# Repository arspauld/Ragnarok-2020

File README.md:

# Ragnarok-2020
Repository containing all software and electronics for the 2020 International CanSat Competition Team Ragnarok. Software is based around the STM32 family of ARM microcontrollers. All electronics are designed to meet the mission requirements described [here](http://cansatcompetition.com/docs/CanSat_Mission_Guide_2020.pdf).

__All mission reviews and documentation are currently hosted separately__.

### Software
#### Pat needs to fill this in
Development is being done in VSCode using the PlatformIO extension.
Requirements/configuration: _something about python, pip, pyserial, etc..._
`sudo apt-get install python3 -m pip`
`pip3 install pyserial`

Software team:
- Patrick Smith (lead)
- Noah Schwalb

For more information about software development contact __PATS INFO HERE__

### Electrical
Electrical development is completed using [KiCad](http://www.kicad.org).

#### Documentation
The directory `/hardware/documentation/` contains important datasheets and application notes for the microcontrollers and components to be used within this project. These documents contain application specific information, and they should contain answers to any questions that may be had about these components.

#### Trade studies
The directory `/hardware/trade-studies/` contains datasheets for each of the sensors considered in this project. Detailed trade-studies have been completed and are hosted outside of this repository.

#### Libraries
The directory `/hardware/libraries/` contains the part libraries to be used within each of the PCBs. These libraries will include schematic symbols and physical footprints for each component. Libraries are first drawn from the [KiCad](http://kicad.org/libraries/download/) standard library and [Digikey-KiCad](https://www.digikey.com/en/resources/design-tools/kicad) standard library. If a symbol or footprint is missing from this library, [SnapEDA](https://www.snapeda.com) will be the next resource used. If the component cannot be found in any of the previous sources, a custom footprint/symbol will be created and housed within a `ragnarok_custom_components` library.

Electrical team:
- Alex Spaulding (lead)
- Shelby Westrich
- Brennan Haralson
- Shelby Tull

For more information about hardware development contact Alex Spaulding at ars0043@uah.edu

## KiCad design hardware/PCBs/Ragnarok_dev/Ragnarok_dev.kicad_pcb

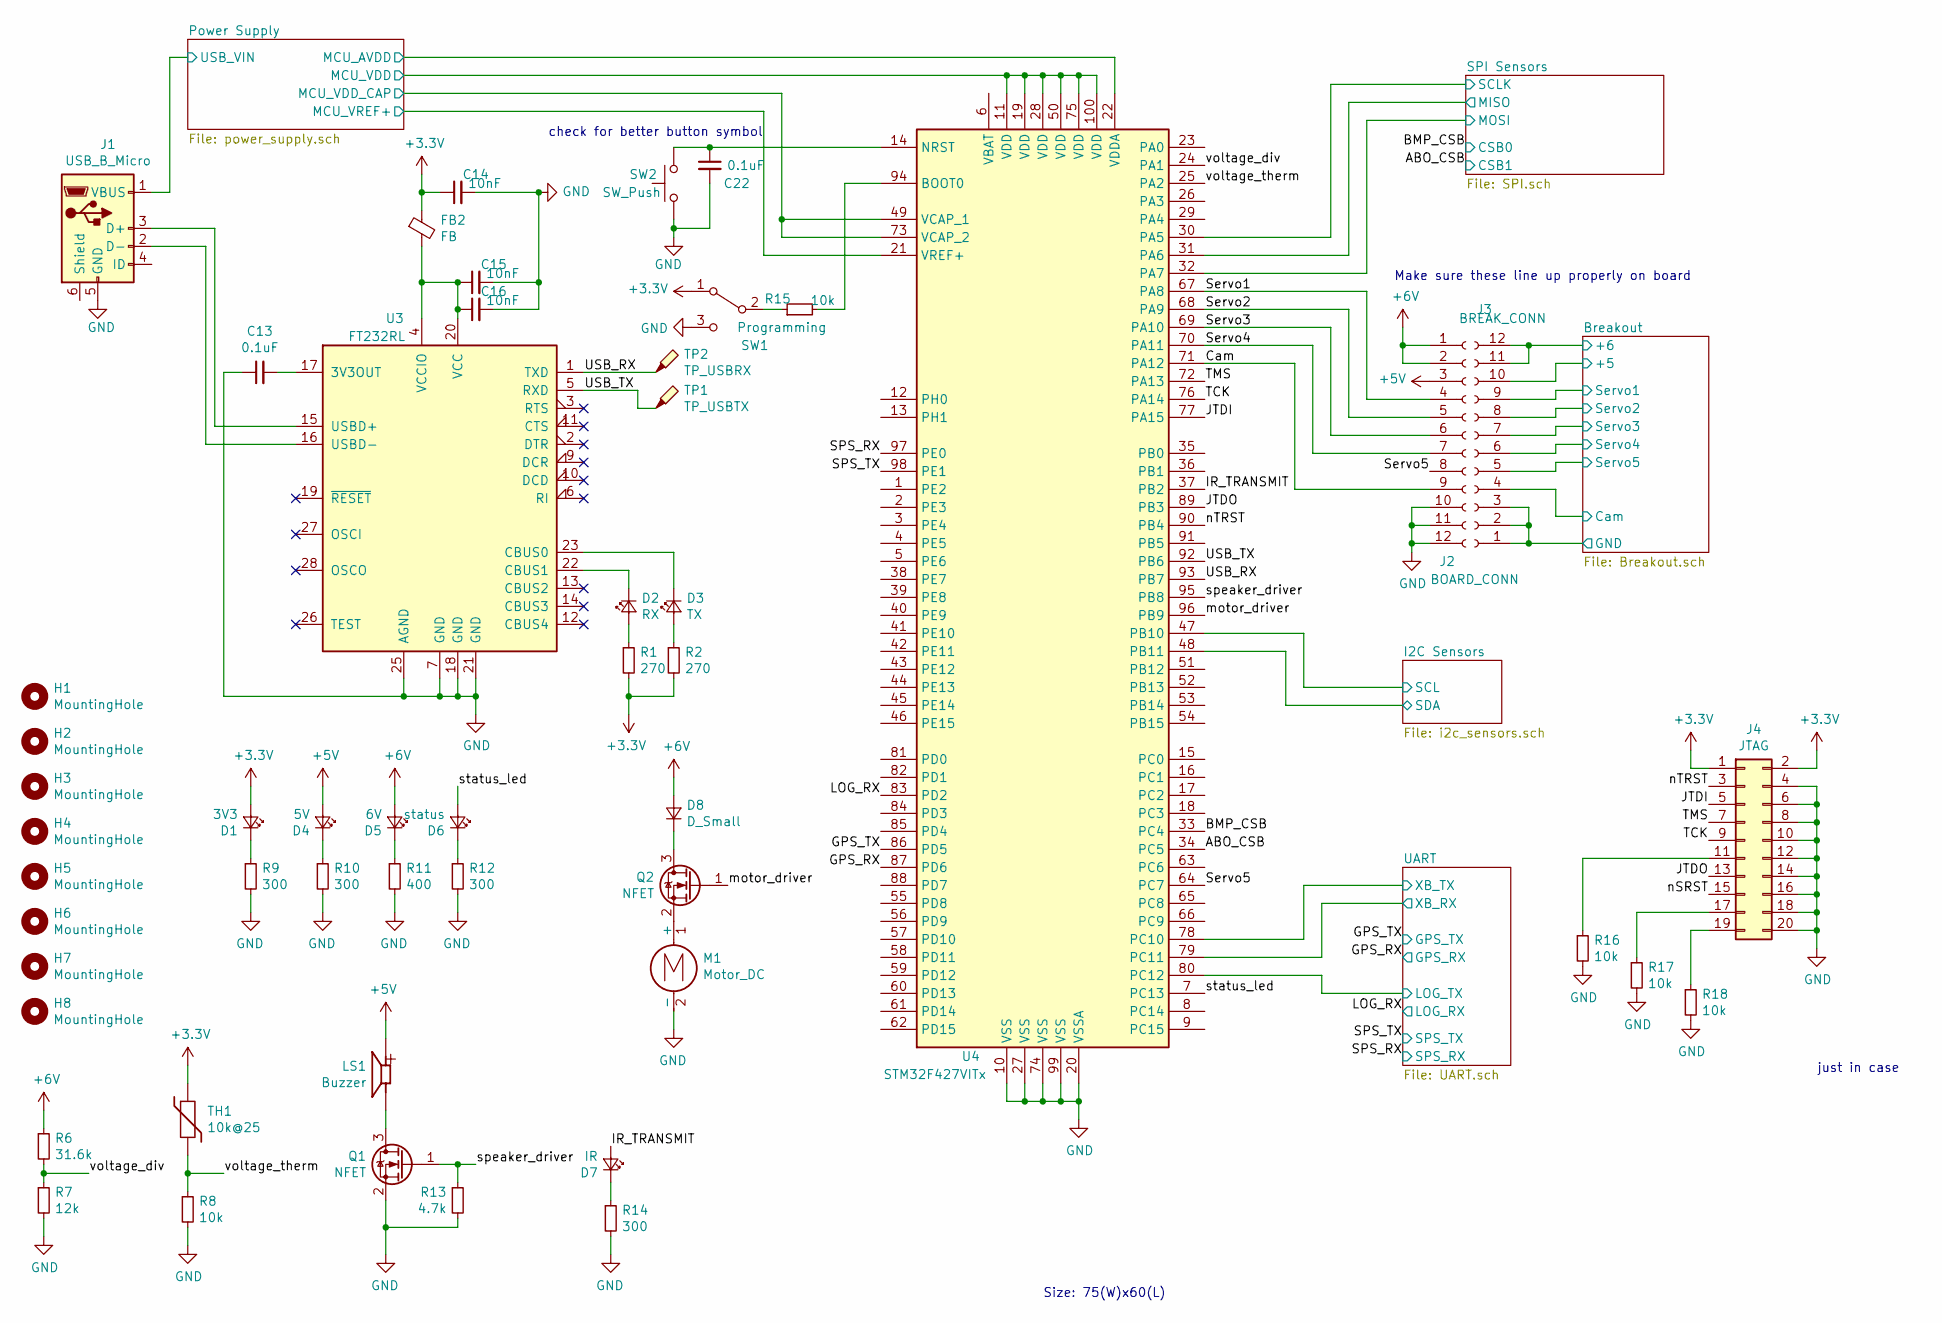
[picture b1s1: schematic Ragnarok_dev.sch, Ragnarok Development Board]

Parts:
C13, C22: 0.1uF; C_0603_1608Metric_Pad1.05x0.95mm_HandSolder
C14, C15, C16: 10nF; C_0603_1608Metric_Pad1.05x0.95mm_HandSolder
D1: 3V3; LED_0603_1608Metric_Pad1.05x0.95mm_HandSolder
D2: RX; LED_0603_1608Metric_Pad1.05x0.95mm_HandSolder
D3: TX; LED_0603_1608Metric_Pad1.05x0.95mm_HandSolder
D4: 5V; LED_0603_1608Metric_Pad1.05x0.95mm_HandSolder
D5: 6V; LED_0603_1608Metric_Pad1.05x0.95mm_HandSolder
D6: status; LED_0603_1608Metric_Pad1.05x0.95mm_HandSolder
D7: IR; JST_GH_SM02B-GHS-TB_1x02-1MP_P1.25mm_Horizontal
D8: D_Small; D_0603_1608Metric_Pad1.05x0.95mm_HandSolder
FB2: FB; L_0603_1608Metric_Pad1.05x0.95mm_HandSolder
H1, H2, H3, H4, H5, H6, H7, H8: MountingHole; MountingHole_2.2mm_M2
J1: USB_B_Micro; USB_Micro-B_Amphenol_10103594-0001LF_Horizontal
J2: BOARD_CONN; Board_Jumper
J3: BREAK_CONN; Board_Jumper
J4: JTAG; PinSocket_2x10_P2.00mm_Vertical
LS1: Buzzer; CUI_CMT-8540S-SMT
M1: Motor_DC; JST_GH_SM02B-GHS-TB_1x02-1MP_P1.25mm_Horizontal
Q1, Q2: NFET; SOT-23_Handsoldering
R1, R2: 270; R_0603_1608Metric_Pad1.05x0.95mm_HandSolder
R6: 31.6k; R_0603_1608Metric_Pad1.05x0.95mm_HandSolder
R7: 12k; R_0603_1608Metric_Pad1.05x0.95mm_HandSolder
R8, R15, R16, R17, R18: 10k; R_0603_1608Metric_Pad1.05x0.95mm_HandSolder
R9, R10, R12, R14: 300; R_0603_1608Metric_Pad1.05x0.95mm_HandSolder
R11: 400; R_0603_1608Metric_Pad1.05x0.95mm_HandSolder
R13: 4.7k; R_0603_1608Metric_Pad1.05x0.95mm_HandSolder
SW1: Programming; CS12ANW03
SW2: SW_Push; SW_SPST_B3SL-1022P
TH1: 10k@25; JST_GH_SM02B-GHS-TB_1x02-1MP_P1.25mm_Horizontal
TP1: TP_USBTX; TestPoint_Pad_1.0x1.0mm
TP2: TP_USBRX; TestPoint_Pad_1.0x1.0mm
U3: FT232RL; SSOP-28_5.3x10.2mm_P0.65mm
U4: STM32F427VITx; LQFP-100_14x14mm_P0.5mm

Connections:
+3V3: C14.1, D1.2 (A), FB2.1, J4.1, J4.2, R1.2, R2.2, SW1.1 (A), TH1.1, U4.11 (VDD), U4.19 (VDD), U4.21 (VREF+), U4.28 (VDD), U4.49 (VCAP_1), U4.50 (VDD), U4.73 (VCAP_2), U4.75 (VDD), U4.100 (VDD); also elsewhere on the board
+5V: D4.2 (A), J2.3, LS1.P; also elsewhere on the board
+6V: D5.2 (A), D8.2 (A), J2.1, J2.2, R6.1; also elsewhere on the board
/ABO_CSB: U4.34 (PC5); also elsewhere on the board
/BMP_CSB: U4.33 (PC4); also elsewhere on the board
/Breakout/+5: J3.10; also elsewhere on the board
/Breakout/+6: J3.11, J3.12; also elsewhere on the board
/Breakout/Cam: J3.4; also elsewhere on the board
/Breakout/Servo1: J3.9; also elsewhere on the board
/Breakout/Servo2: J3.8; also elsewhere on the board
/Breakout/Servo3: J3.7; also elsewhere on the board
/Breakout/Servo4: J3.6; also elsewhere on the board
/Breakout/Servo5: J3.5; also elsewhere on the board
/Cam: J2.9, U4.71 (PA12)
/GPS_RX: U4.87 (PD6); also elsewhere on the board
/GPS_TX: U4.86 (PD5); also elsewhere on the board
/I2C Sensors/SCL: U4.47 (PB10); also elsewhere on the board
/I2C Sensors/SDA: U4.48 (PB11); also elsewhere on the board
/IR_TRANSMIT: D7.2 (A), U4.37 (PB2)
/JTDI: J4.5, U4.77 (PA15)
/JTDO: J4.13, U4.89 (PB3)
/LOG_RX: U4.83 (PD2); also elsewhere on the board
/Power Supply/MCU_AVDD: U4.22 (VDDA); also elsewhere on the board
/Power Supply/USB_VIN: J1.1 (VBUS); also elsewhere on the board
/SPI Sensors/MISO: U4.31 (PA6); also elsewhere on the board
/SPI Sensors/MOSI: U4.32 (PA7); also elsewhere on the board
/SPI Sensors/SCLK: U4.30 (PA5); also elsewhere on the board
/SPS_RX: U4.97 (PE0); also elsewhere on the board
/SPS_TX: U4.98 (PE1); also elsewhere on the board
/Servo1: J2.4, U4.67 (PA8)
/Servo2: J2.5, U4.68 (PA9)
/Servo3: J2.6, U4.69 (PA10)
/Servo4: J2.7, U4.70 (PA11)
/Servo5: J2.8, U4.64 (PC7)
/TCK: J4.9, U4.76 (PA14)
/TMS: J4.7, U4.72 (PA13)
/UART/LOG_TX: U4.80 (PC12); also elsewhere on the board
/UART/XB_RX: U4.79 (PC11); also elsewhere on the board
/UART/XB_TX: U4.78 (PC10); also elsewhere on the board
/USB_RX: TP2.1, U3.1 (TXD), U4.93 (PB7)
/USB_TX: TP1.1, U3.5 (RXD), U4.92 (PB6)
/motor_driver: Q2.1 (G), U4.96 (PB9)
/nSRST: J4.15
/nTRST: J4.3, U4.90 (PB4)
/speaker_driver: Q1.1 (G), R13.1, U4.95 (PB8)
/status_led: D6.2 (A), U4.7 (PC13)
/voltage_div: R6.2, R7.1, U4.24 (PA1)
/voltage_therm: R8.1, TH1.2, U4.25 (PA2)
GND: C13.1, C14.2, C15.2, C16.2, C22.2, J1.5 (GND), J2.10, J2.11, J2.12, J3.1, J3.2, J3.3, J4.4, J4.6, J4.8, J4.10, J4.12, J4.14, J4.16, J4.18, J4.20, M1.2 (-), Q1.2 (S), R7.2, R8.2, R9.2, R10.2, R11.2, R12.2, R13.2, R14.2, R16.2, R17.2, R18.2, SW1.3 (C), SW2.2, U3.7 (GND), U3.18 (GND), U3.21 (GND), U3.25 (AGND), U4.10 (VSS), U4.20 (VSSA), U4.27 (VSS), U4.74 (VSS), U4.99 (VSS); also elsewhere on the board
unnamed: C13.2, U3.17 (3V3OUT)
unnamed: C15.1, C16.1, FB2.2, U3.4 (VCCIO), U3.20 (VCC)
unnamed: C22.1, SW2.1, U4.14 (NRST)
unnamed: D1.1 (K), R9.1
unnamed: D2.1 (K), U3.22 (CBUS1)
unnamed: D2.2 (A), R1.1
unnamed: D3.1 (K), U3.23 (CBUS0)
unnamed: D3.2 (A), R2.1
unnamed: D4.1 (K), R10.1
unnamed: D5.1 (K), R11.1
unnamed: D6.1 (K), R12.1
unnamed: D7.1 (K), R14.1
unnamed: D8.1 (K), Q2.3 (D)
unnamed: J1.2 (D-), U3.16 (USBD-)
unnamed: J1.3 (D+), U3.15 (USBD+)
unnamed: J4.11, R16.1
unnamed: J4.17, R17.1
unnamed: J4.19, R18.1
unnamed: LS1.N, Q1.3 (D)
unnamed: M1.1 (+), Q2.2 (S)
unnamed: R15.1, SW1.2 (B)
unnamed: R15.2, U4.94 (BOOT0)

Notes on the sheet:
Make sure these line up properly on board
check for better button symbol
just in case
Size: 75(W)x60(L)

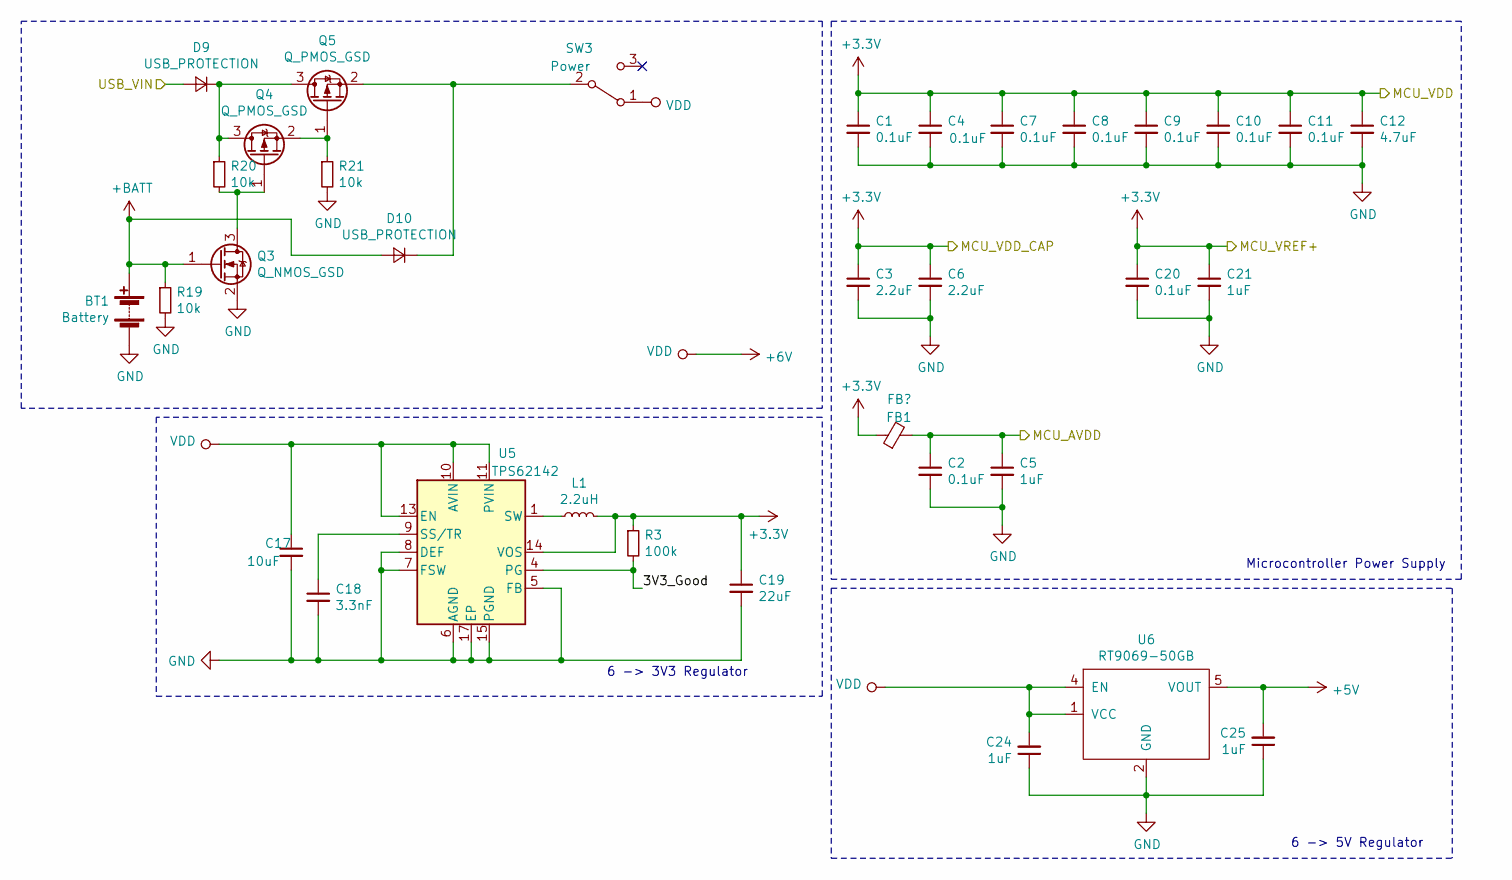
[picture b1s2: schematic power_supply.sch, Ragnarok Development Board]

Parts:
BT1: Battery; JST_GH_SM02B-GHS-TB_1x02-1MP_P1.25mm_Horizontal
C1, C2, C4, C7, C8, C9, C10, C11, C20: 0.1uF; C_0603_1608Metric_Pad1.05x0.95mm_HandSolder
C3, C6: 2.2uF; C_0603_1608Metric_Pad1.05x0.95mm_HandSolder
C5, C21, C24, C25: 1uF; C_0603_1608Metric_Pad1.05x0.95mm_HandSolder
C12: 4.7uF; C_0603_1608Metric_Pad1.05x0.95mm_HandSolder
C17: 10uF; C_0603_1608Metric_Pad1.05x0.95mm_HandSolder
C18: 3.3nF; C_0603_1608Metric_Pad1.05x0.95mm_HandSolder
C19: 22uF; C_0603_1608Metric_Pad1.05x0.95mm_HandSolder
D9, D10: USB_PROTECTION; D_0603_1608Metric_Pad1.05x0.95mm_HandSolder
FB1: FB?; L_0603_1608Metric_Pad1.05x0.95mm_HandSolder
L1: 2.2uH; L_0603_1608Metric_Pad1.05x0.95mm_HandSolder
Q3: Q_NMOS_GSD; SOT-23_Handsoldering
Q4, Q5: Q_PMOS_GSD; SOT-23_Handsoldering
R3: 100k; R_0603_1608Metric_Pad1.05x0.95mm_HandSolder
R19, R20, R21: 10k; R_0603_1608Metric_Pad1.05x0.95mm_HandSolder
SW3: Power; CS12ANW03
U5: TPS62142; QFN-16-1EP_3x3mm_P0.5mm_EP1.8x1.8mm
U6: RT9069-50GB; SOT-23-5

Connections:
+3V3: C1.1, C3.1, C4.1, C6.1, C7.1, C8.1, C9.1, C10.1, C11.1, C12.1, C19.1, C20.1, C21.1, FB1.1, L1.2, R3.1, U5.14 (VOS); also elsewhere on the board
+5V: C25.2, U6.5 (VOUT); also elsewhere on the board
+6V: C17.1, C24.2, SW3.1 (A), U5.10 (AVIN), U5.11 (PVIN), U5.12 (PVIN), U5.13 (EN), U6.1 (VCC), U6.4 (EN); also elsewhere on the board
+BATT: BT1.1 (+), D10.2 (A), Q3.1 (G), R19.1
/Power Supply/3V3_Good: R3.2, U5.4 (PG)
/Power Supply/MCU_AVDD: C2.1, C5.1, FB1.2; also elsewhere on the board
/Power Supply/USB_VIN: D9.2 (A); also elsewhere on the board
GND: BT1.2 (-), C1.2, C2.2, C3.2, C4.2, C5.2, C6.2, C7.2, C8.2, C9.2, C10.2, C11.2, C12.2, C17.2, C18.2, C19.2, C20.2, C21.2, C24.1, C25.1, Q3.2 (S), R19.2, R21.2, U5.5 (FB), U5.6 (AGND), U5.7 (FSW), U5.8 (DEF), U5.15 (PGND), U5.16 (PGND), U5.17 (EP), U6.2 (GND); also elsewhere on the board
unnamed: C18.1, U5.9 (SS/TR)
unnamed: D9.1 (K), Q4.3 (D), Q5.3 (D), R20.1
unnamed: D10.1 (K), Q5.2 (S), SW3.2 (B)
unnamed: L1.1, U5.1 (SW), U5.2 (SW), U5.3 (SW)
unnamed: Q3.3 (D), Q4.1 (G), R20.2
unnamed: Q4.2 (S), Q5.1 (G), R21.1

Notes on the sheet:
Microcontroller Power Supply
6 -> 3V3 Regulator
6 -> 5V Regulator

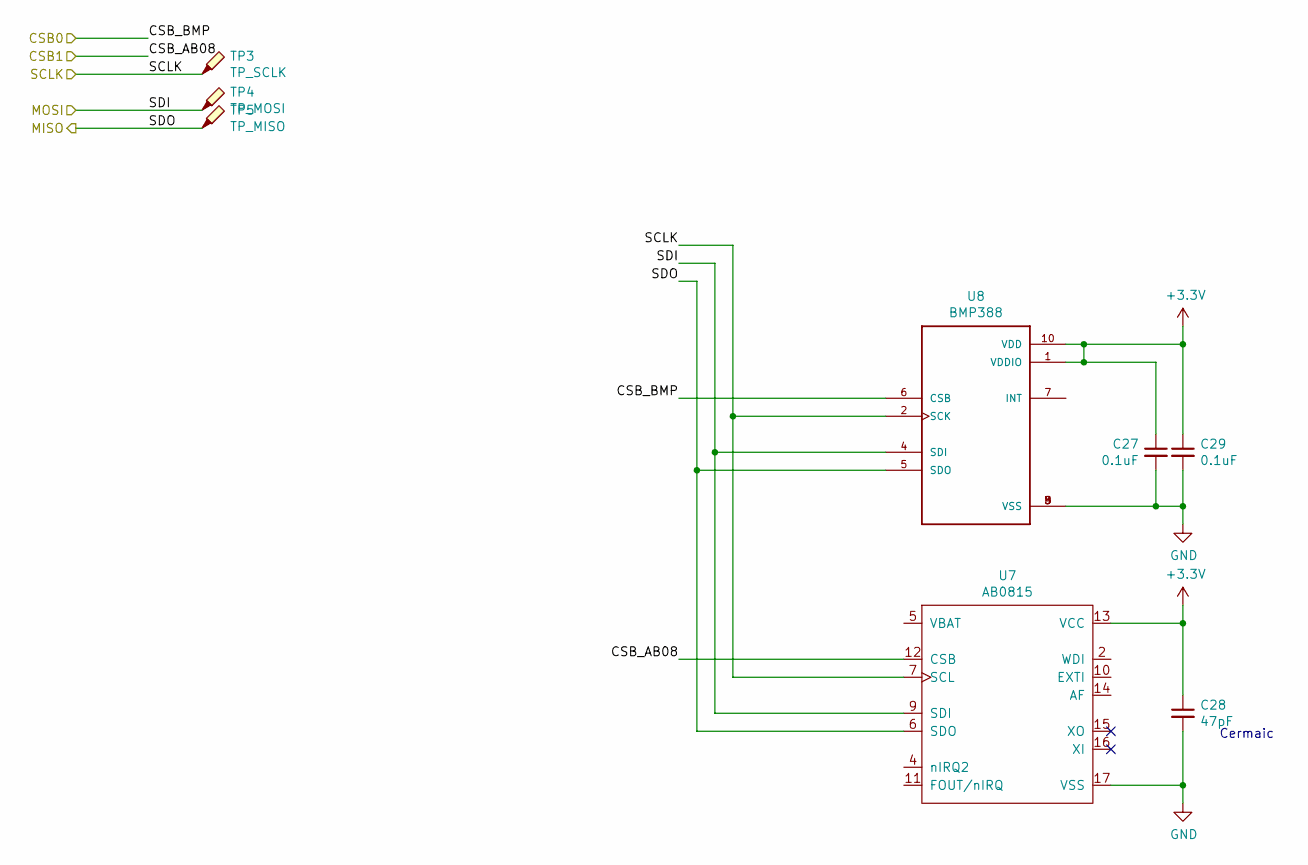
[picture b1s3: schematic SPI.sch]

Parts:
C27, C29: 0.1uF; C_0603_1608Metric_Pad1.05x0.95mm_HandSolder
C28: 47pF; C_0603_1608Metric_Pad1.05x0.95mm_HandSolder
TP3: TP_SCLK; TestPoint_Pad_1.0x1.0mm
TP4: TP_MOSI; TestPoint_Pad_1.0x1.0mm
TP5: TP_MISO; TestPoint_Pad_1.0x1.0mm
U7: AB0815; QFN-16-1EP_5x5mm_P0.8mm_EP2.7x2.7mm
U8: BMP388; PQFN50P200X200X80-10N

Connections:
+3V3: C27.1, C28.1, C29.1, U7.13 (VCC), U8.1 (VDDIO), U8.10 (VDD); also elsewhere on the board
/ABO_CSB: U7.12 (CSB); also elsewhere on the board
/BMP_CSB: U8.6 (CSB); also elsewhere on the board
/SPI Sensors/MISO: TP5.1, U7.6 (SDO), U8.5 (SDO); also elsewhere on the board
/SPI Sensors/MOSI: TP4.1, U7.9 (SDI), U8.4 (SDI); also elsewhere on the board
/SPI Sensors/SCLK: TP3.1, U7.7 (SCL), U8.2 (SCK); also elsewhere on the board
GND: C27.2, C28.2, C29.2, U7.17 (VSS), U8.3 (VSS), U8.8 (VSS), U8.9 (VSS); also elsewhere on the board

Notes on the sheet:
Cermaic

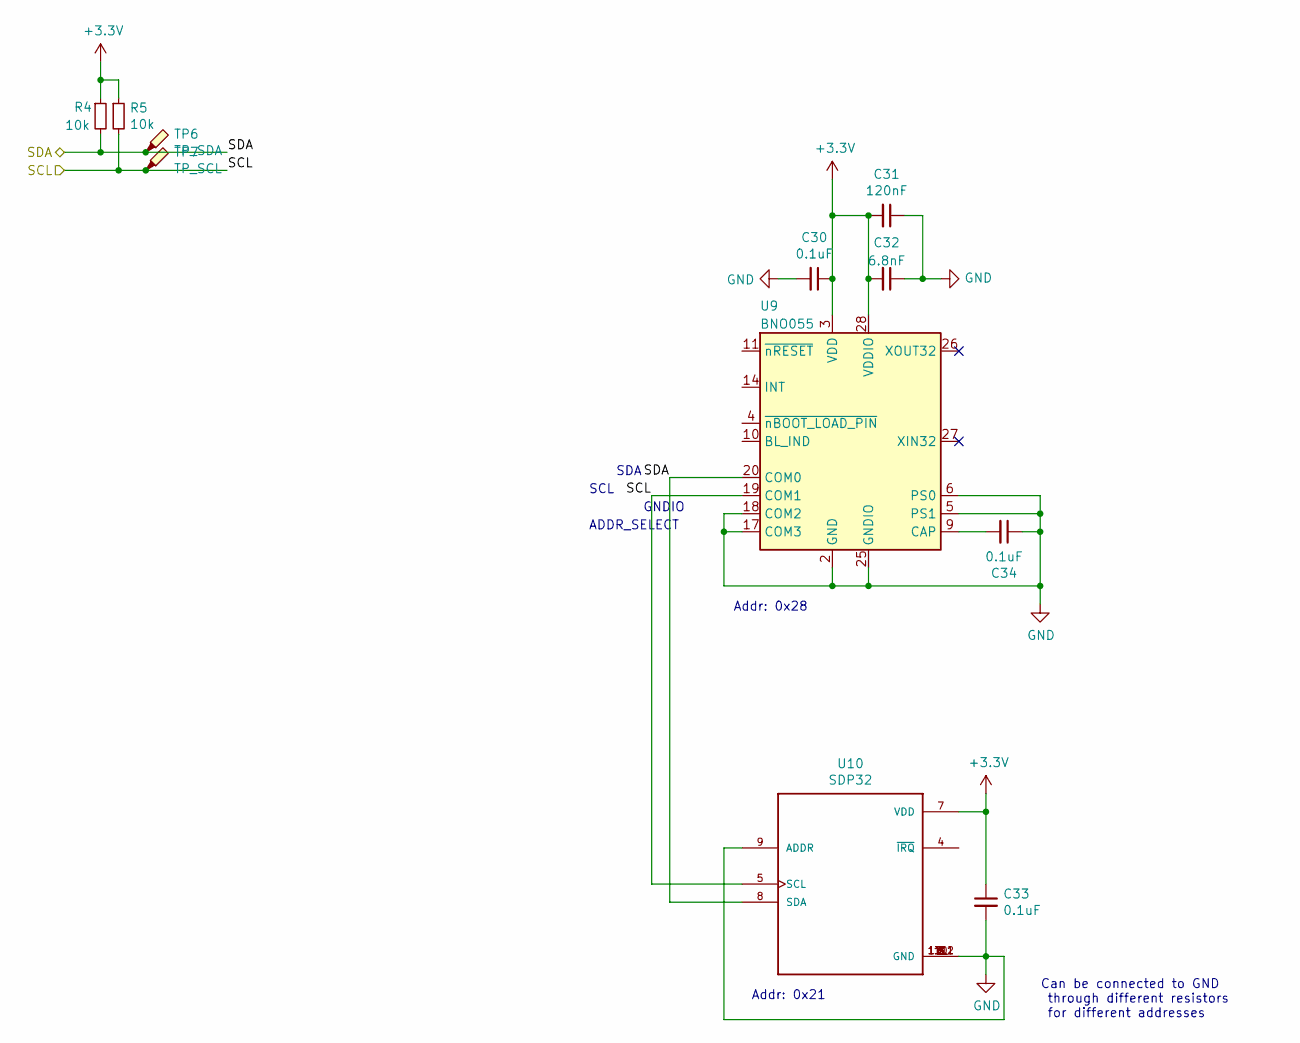
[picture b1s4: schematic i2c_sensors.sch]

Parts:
C30, C33, C34: 0.1uF; C_0603_1608Metric_Pad1.05x0.95mm_HandSolder
C31: 120nF; C_0603_1608Metric_Pad1.05x0.95mm_HandSolder
C32: 6.8nF; C_0603_1608Metric_Pad1.05x0.95mm_HandSolder
R4, R5: 10k; R_0603_1608Metric_Pad1.05x0.95mm_HandSolder
TP6: TP_SDA; TestPoint_Pad_1.0x1.0mm
TP7: TP_SCL; TestPoint_Pad_1.0x1.0mm
U9: BNO055; LGA-28_5.2x3.8mm_P0.5mm
U10: SDP32; XDCR_SDP32-125PA-TR-250PCS

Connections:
+3V3: C30.1, C31.2, C32.2, C33.1, R4.1, R5.1, U9.3 (VDD), U9.28 (VDDIO), U10.7 (VDD); also elsewhere on the board
/I2C Sensors/SCL: R5.2, TP7.1, U9.19 (COM1), U10.5 (SCL); also elsewhere on the board
/I2C Sensors/SDA: R4.2, TP6.1, U9.20 (COM0), U10.8 (SDA); also elsewhere on the board
GND: C30.2, C31.1, C32.1, C33.2, C34.1, U9.2 (GND), U9.5 (PS1), U9.6 (PS0), U9.15 (GNDIO), U9.16 (GNDIO), U9.17 (COM3), U9.18 (COM2), U9.25 (GNDIO), U10.1 (GND), U10.2 (GND), U10.3 (GND), U10.6 (GND), U10.9 (ADDR), U10.10 (GND), U10.11 (GND), U10.17_1 (GND), U10.17_2 (GND); also elsewhere on the board
unnamed: C34.2, U9.9 (CAP)

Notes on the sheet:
Can be connected to GND through different resistors for different addresses
SDA
SCL
ADDR_SELECT
GNDIO
Addr: 0x28
Addr: 0x21

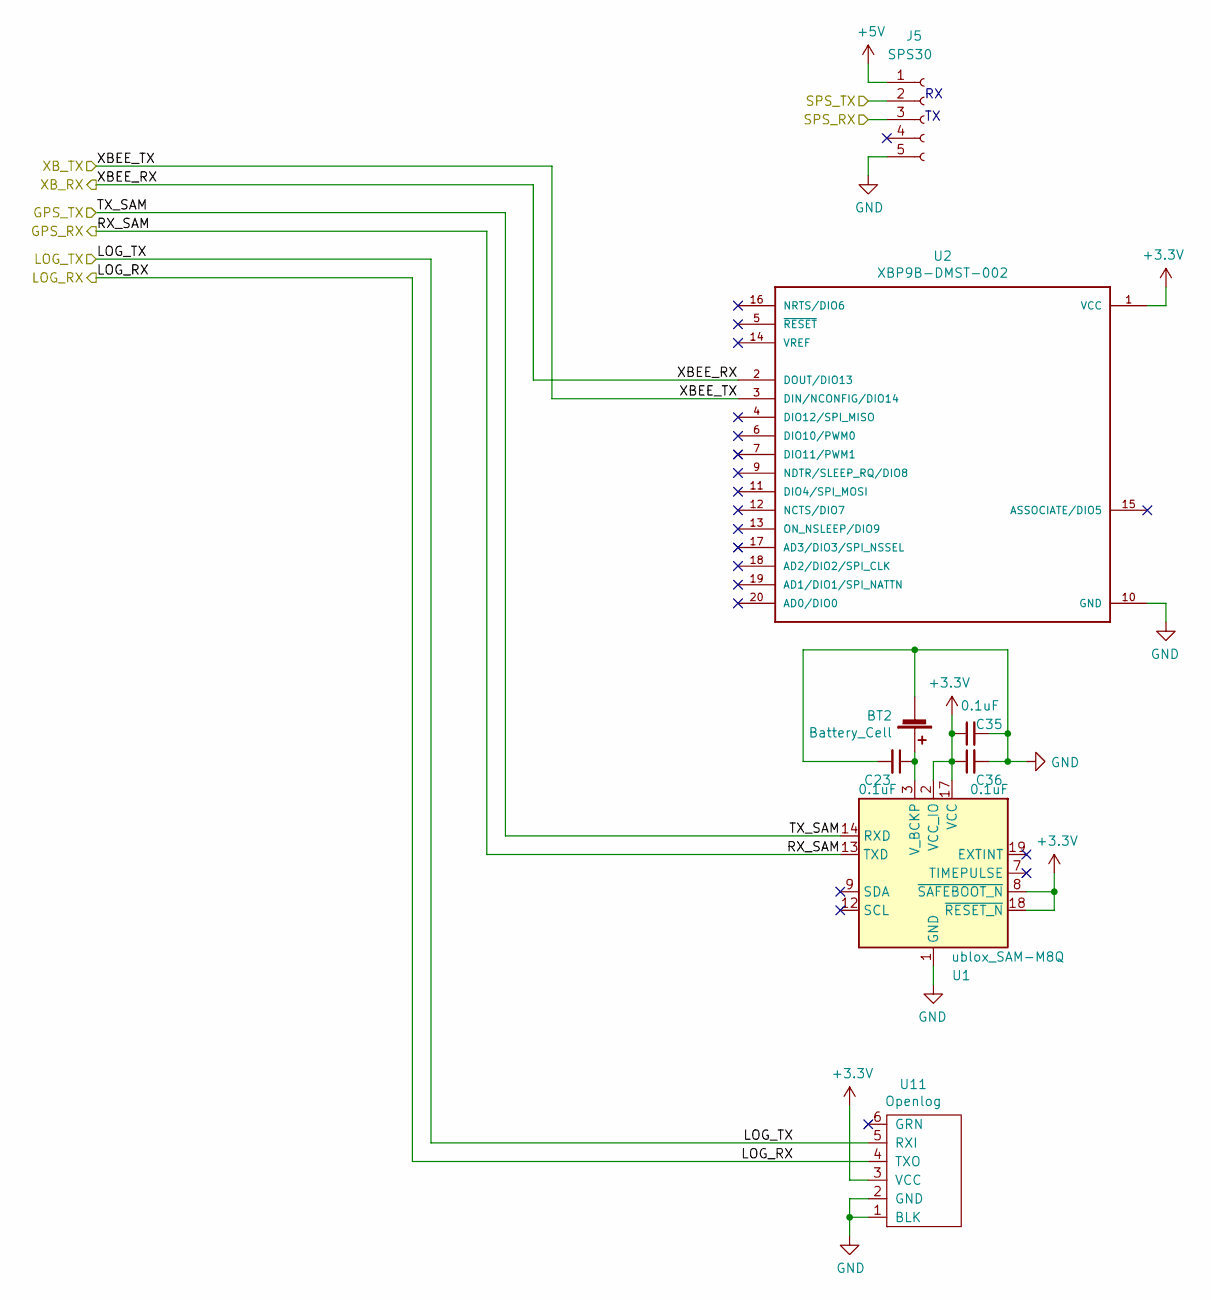
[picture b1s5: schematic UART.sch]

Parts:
BT2: Battery_Cell
C23, C35, C36: 0.1uF; C_0603_1608Metric_Pad1.05x0.95mm_HandSolder
J5: SPS30; JST_GH_SM05B-GHS-TB_1x05-1MP_P1.25mm_Horizontal
U1: ublox_SAM-M8Q; ublox_SAM-M8Q_HandSolder
U2: XBP9B-DMST-002; DIP2200W51P200L3294H279Q20P
U11: Openlog; PinHeader_1x06_P2.54mm_Vertical

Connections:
+3V3: C35.1, C36.1, U1.2 (VCC_IO), U1.8 (~SAFEBOOT_N), U1.17 (VCC), U1.18 (~RESET_N), U2.1 (VCC), U11.3 (VCC); also elsewhere on the board
+5V: J5.1; also elsewhere on the board
/GPS_RX: U1.13 (TXD); also elsewhere on the board
/GPS_TX: U1.14 (RXD); also elsewhere on the board
/LOG_RX: U11.4 (TXO); also elsewhere on the board
/SPS_RX: J5.3; also elsewhere on the board
/SPS_TX: J5.2; also elsewhere on the board
/UART/LOG_TX: U11.5 (RXI); also elsewhere on the board
/UART/XB_RX: U2.2 (DOUT/DIO13); also elsewhere on the board
/UART/XB_TX: U2.3 (DIN/NCONFIG/DIO14); also elsewhere on the board
GND: BT2.2 (-), C23.2, C35.2, C36.2, J5.5, U1.1 (GND), U1.4 (GND), U1.5 (GND), U1.6 (GND), U1.10 (GND), U1.11 (GND), U1.15 (GND), U1.16 (GND), U1.20 (GND), U2.10 (GND), U11.1 (BLK), U11.2 (GND); also elsewhere on the board
unnamed: BT2.1 (+), C23.1, U1.3 (V_BCKP)

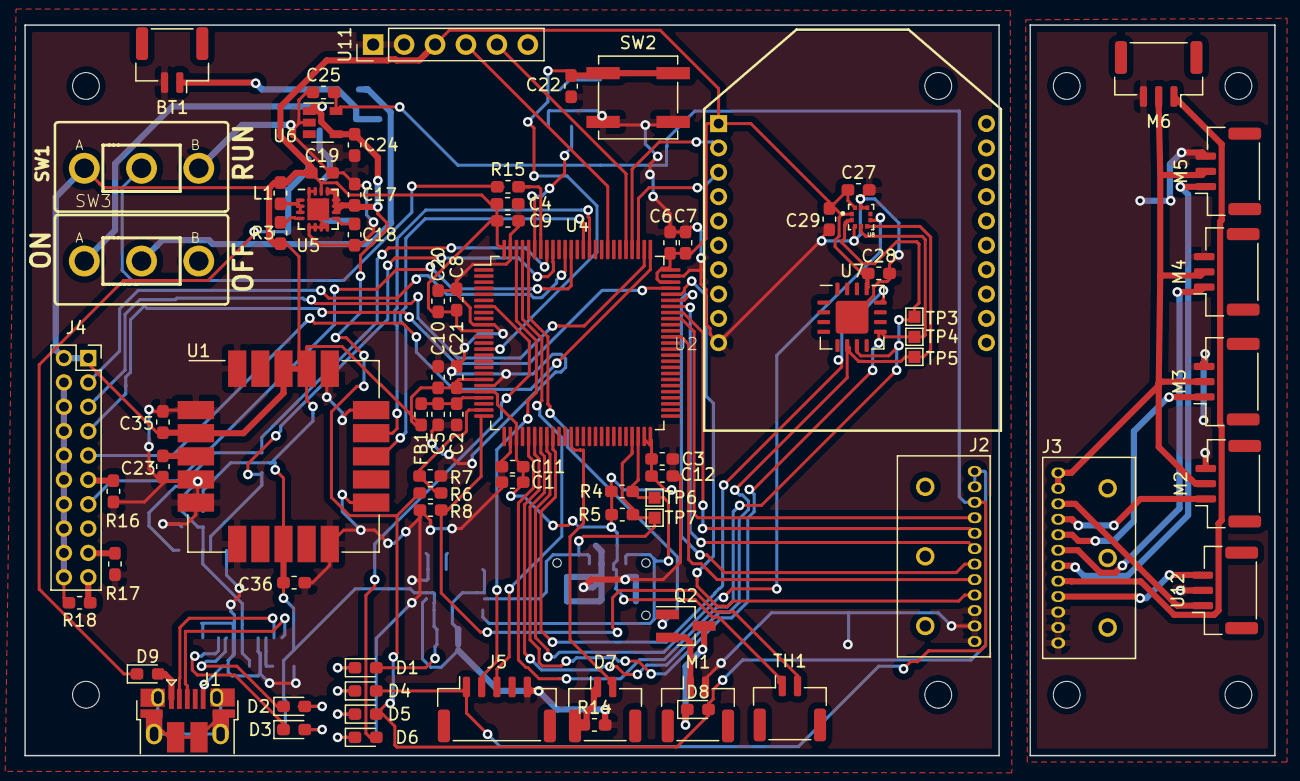
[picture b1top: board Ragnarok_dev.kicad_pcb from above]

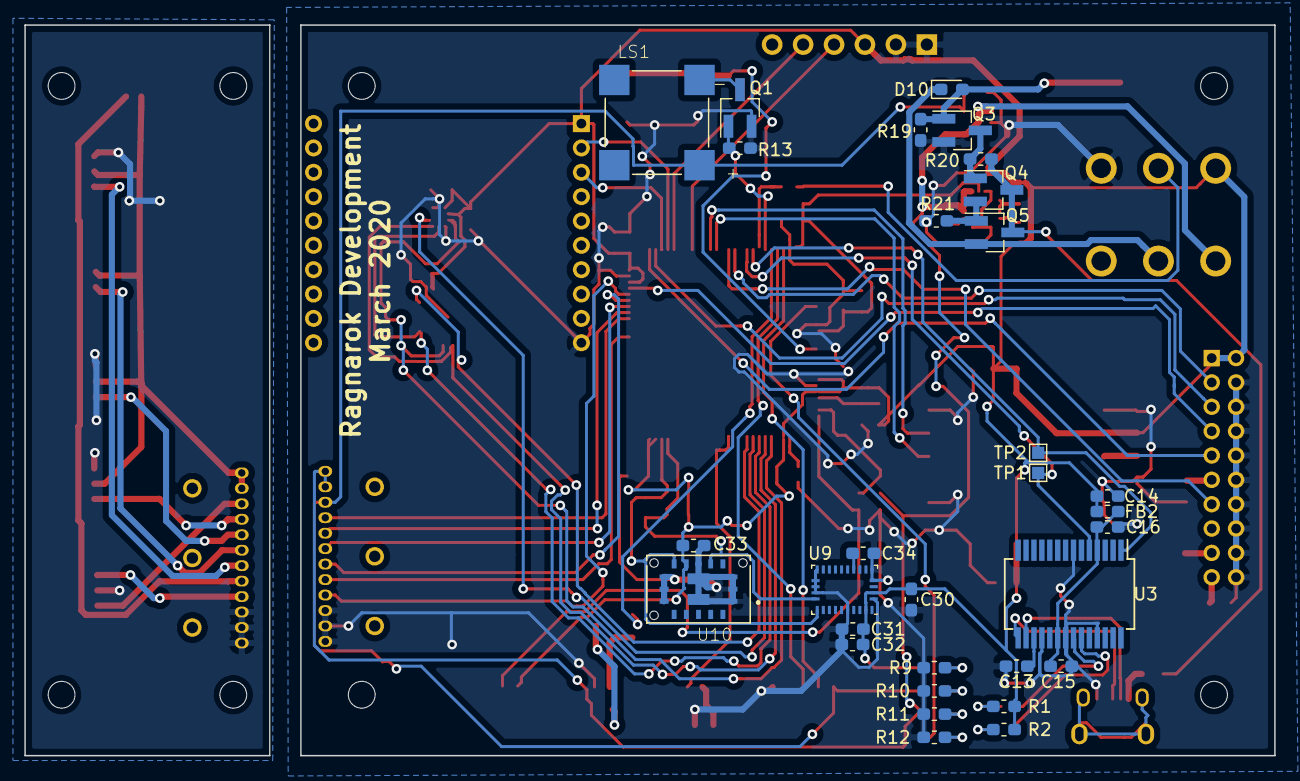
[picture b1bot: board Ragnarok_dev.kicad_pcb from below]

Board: 2 copper layers, 102.7 x 60.0 mm, 118 parts (31 on the bottom side), 80 nets.

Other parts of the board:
M2, M3, M4, M5, M6: Motor_Servo; JST_GH_SM03B-GHS-TB_1x03-1MP_P1.25mm_Horizontal
U12: MiniSpy; JST_GH_SM03B-GHS-TB_1x03-1MP_P1.25mm_Horizontal

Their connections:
/Breakout/+5: U12.1; also elsewhere on the board
/Breakout/+6: M2.2, M3.2, M4.2, M5.2, M6.2; also elsewhere on the board
/Breakout/Cam: U12.3; also elsewhere on the board
/Breakout/Servo1: M2.1; also elsewhere on the board
/Breakout/Servo2: M3.1; also elsewhere on the board
/Breakout/Servo3: M4.1; also elsewhere on the board
/Breakout/Servo4: M5.1; also elsewhere on the board
/Breakout/Servo5: M6.1; also elsewhere on the board
GND: M2.3, M3.3, M4.3, M5.3, M6.3, U12.2; also elsewhere on the board

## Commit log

2019-10-03 Initial commit, add hardware notes
2019-10-03 Add temp software file to show directory structure
2019-10-03 include programming manual
2019-10-04 file structure and adding 5607
2019-10-19 Create ina233.pdf
    Added voltage sensor documentation
2019-10-19 Add documentation
    Added pressure sensor documentation
2019-10-19 Add documentation
    added temperature sensor documentation; LM35 datasheet applies to 2 separate sensors
2019-10-19 Add documentation
    Added particulate sensor documentation
2019-10-19 Add documentation for IMUs
2019-10-27 mcu documentation
2019-10-29 altitude conversion script (thanks westy)
2019-10-29 mpl data sheet
2019-10-29 more documentation for trade studies
2019-11-01 mcu application notes
2019-11-05 Made Folders and tested G++ on computer
2019-11-05 moved .exe
2019-11-08 Made Platform IO project
2019-11-08 binary garbage
2019-11-09 update docs
2019-11-10 begin work on custom upload script
2019-11-10 why isnt it working
2019-11-10 Data
2019-11-11 connected over uart and entering basic commands
2019-11-11 almost working upload script
2019-11-11 main.c
2019-11-11 prototyping
2019-11-11 upload script working? Code not executing
2019-11-12 latest
2019-11-12 Edits (0x0010000)
2019-11-12 0x0010000
2019-11-13 upload script is working, need to work on interfacing with platformio and fixing verification
2019-11-14 IT WORKS
2019-11-24 Found documentation
2019-11-24 documentation
2019-12-07 Bare Metal Blink?
2019-12-08 Timer
2019-12-08 120 MHz?
2019-12-08 Succesful Clock Speed Change
2019-12-09 PWM on A0
2019-12-09 Comments and Maybe USART?
2019-12-10 USART (or at least UART) works
2019-12-10 USART
2019-12-11 GPIO Interrupt
2019-12-11 USART Verified
2019-12-11 UART Echo (unstable)
2019-12-11 setup pins for SPI1
2019-12-13 Maybe initialized?
2019-12-14 I2C read?
2019-12-14 built to check for syntactical errors
2019-12-18 I2C read
2019-12-19 TO-DO
2019-12-19 ADC maybe works
2019-12-19 progress
2019-12-19 progress on power supply, USB programming
2019-12-19 ADC Tested and seems to be functional
2019-12-19 TO-DO Update
2019-12-19 System Reset Included
2019-12-19 Removed unused variable
2019-12-19 Changed Baud to work with Serial Monitor in PIO
2019-12-20 minor changes
2019-12-20 sketchy FLASH memory
2019-12-20 Made it so the variable was a 32 bit integer
2019-12-21 Made Flash Less Sketchy
2019-12-24 ground_station updates
    this is what I have so far, I have not spent too much time so bare with me
2019-12-24 Worked on include files
2019-12-24 Moved files and made Flash files
2019-12-25 Moved functions to dedicated files to show goal
2019-12-25 Fleshed out USARt file more, more work to come
2019-12-26 More work on USART options and peripheral function
2019-12-28 fixed RTP inheritance, testclass works for groundstation.py
2019-12-31 Removed space
2019-12-31 Eh, not much work done
2020-01-05 added parameters for window resizing, added the paramters to testclass
2020-01-05 changed case of dock titles
2020-01-05 deleted some unneeded lines, added comments to functions
2020-01-06 changed testclass name
2020-01-06 small edits
2020-01-10 add spi sheet
2020-01-17 Numbered Pins and Descent Rate Calculator
2020-01-21 Simulation slides
2020-01-27 UART
2020-01-29 replace 5v regulator
2020-02-07 work
2020-02-26 much schematic work
2020-03-03 add missing libraries, need more
2020-03-03 todos
2020-03-05 idk man
2020-03-06 finish schematic
2020-03-07 begin layout
2020-03-09 first PCB
2020-03-13 final changes
